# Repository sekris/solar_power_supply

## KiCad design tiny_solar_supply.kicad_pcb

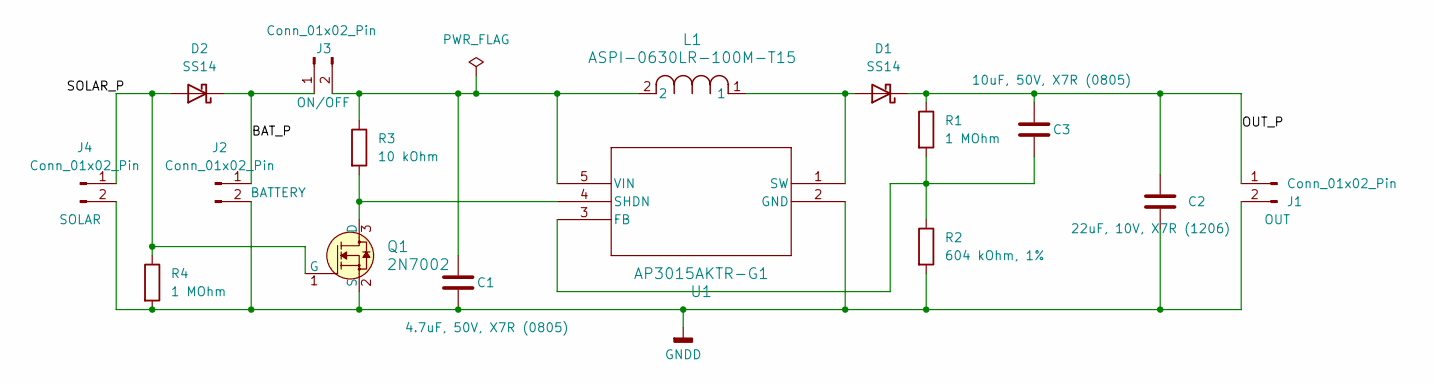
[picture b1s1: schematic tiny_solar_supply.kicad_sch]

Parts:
C1: 4.7uF, 50V, X7R (0805); C_0805_2012Metric
C2: 22uF, 10V, X7R (1206); C_1206_3216Metric
C3: 10uF, 50V, X7R (0805); C_0805_2012Metric
D1, D2: SS14; D_SMA
J1, J2, J3, J4: Conn_01x02_Pin; PinHeader_1x02_P2.54mm_Vertical
L1: ASPI-0630LR-100M-T15; IND_ASPI-0630LR_ABR-M
Q1: 2N7002; SOT-23-3; MPN 2N7002; Digi-Key_PN 2N7002NCT-ND
R1, R4: 1 MOhm; R_0805_2012Metric
R2: 604 kOhm, 1%; R_0805_2012Metric
R3: 10 kOhm; R_0805_2012Metric
U1: AP3015AKTR-G1; SOT23-5_1P55X2P9_DIO

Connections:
/BAT_P: D2.1 (K), J2.1, J3.1
/OUT_P: C2.1, C3.1, D1.1 (K), J1.1, R1.1
/SOLAR_P: D2.2 (A), J4.1, Q1.1 (G), R4.1
GNDD: C1.2, C2.2, J1.2, J2.2, J4.2, Q1.2 (S), R2.2, R4.2, U1.2 (GND)
unnamed: D1.2 (A), L1.1, U1.1 (SW)
unnamed: C1.1, J3.2, L1.2, R3.1, U1.5 (VIN)
unnamed: Q1.3 (D), R3.2, U1.4 (SHDN)
unnamed: C3.2, R1.2, R2.1, U1.3 (FB)

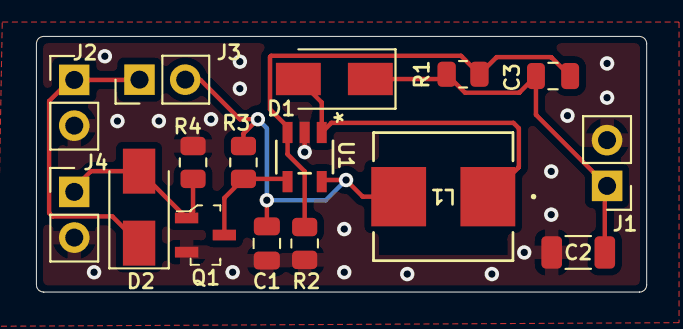
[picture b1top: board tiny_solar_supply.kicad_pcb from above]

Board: 2 copper layers, 33.9 x 14.2 mm, 16 parts (0 on the bottom side), 8 nets.
